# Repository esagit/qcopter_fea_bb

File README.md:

# Quadcopter - Breakout Board Adapter
Quadcopter - Breakout Board for Adafruit Feather 32u4 RFM9x LoRa Radio Module
* [Adafruit Feather 32u4 RFM9x LoRa Radio](https://www.adafruit.com/product/3078)

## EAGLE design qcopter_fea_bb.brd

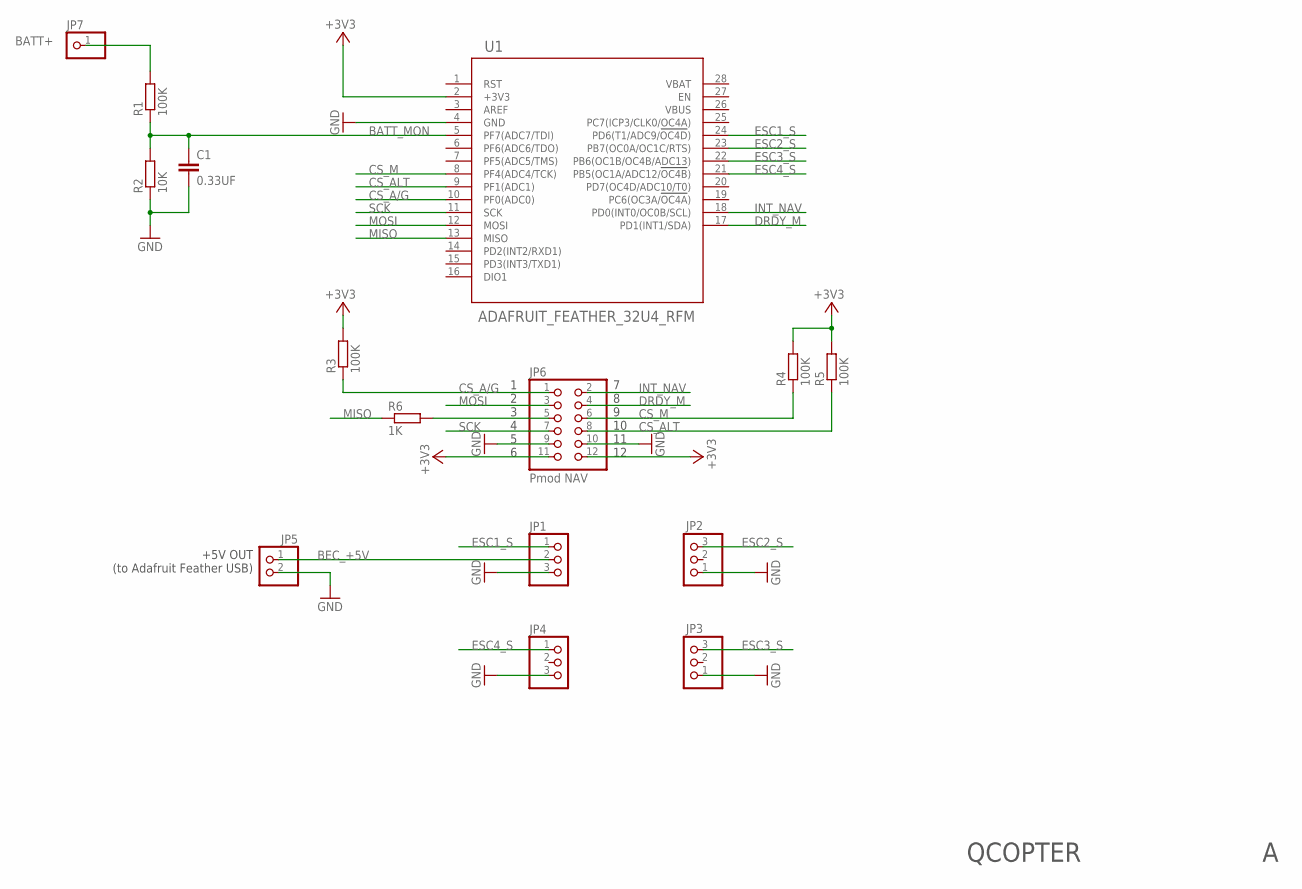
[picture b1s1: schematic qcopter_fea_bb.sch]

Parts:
C1: 0.33UF; C025-025X050
JP1, JP2, JP3, JP4: PINHD-1X3/90; 1X03/90
JP5: PINHD-1X2/90; 1X02/90
JP6: Pmod NAV; 2X06/90
JP7: PINHD-1X1; 1X01
R1, R3, R4, R5: 100K; 0207/10
R2: 10K; 0207/10
R6: 1K; 0207/10
U1: ADAFRUIT_FEATHER_32U4_RFM

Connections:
+3V3: JP6.11, JP6.12, R3.2, R4.2, R5.2, U1.2 (+3V3)
BATT+: JP7.1, R1.2
BATT_MON: C1.1, R1.1, R2.2, U1.5 (PF7(ADC7/TDI))
BEC_+5V: JP1.2, JP5.1
CS_A/G: JP6.1, R3.1, U1.10 (PF0(ADC0))
CS_ALT: JP6.8, R5.1, U1.9 (PF1(ADC1))
CS_M: JP6.6, R4.1, U1.8 (PF4(ADC4/TCK))
DRDY_M: JP6.4, U1.17 (PD1(INT1/SDA))
ESC1_S: JP1.1, U1.24 (PD6(T1/ADC9/OC4D))
ESC2_S: JP2.3, U1.23 (PB7(OC0A/OC1C/RTS))
ESC3_S: JP3.3, U1.22 (PB6(OC1B/OC4B/ADC13))
ESC4_S: JP4.1, U1.21 (PB5(OC1A/ADC12/OC4B))
GND: C1.2, JP1.3, JP2.1, JP3.1, JP4.3, JP5.2, JP6.9, JP6.10, R2.1, U1.4 (GND)
INT_NAV: JP6.2, U1.18 (PD0(INT0/OC0B/SCL))
MISO: R6.1, U1.13 (MISO)
MOSI: JP6.3, U1.12 (MOSI)
unnamed: JP6.5, R6.2
SCK: JP6.7, U1.11 (SCK)

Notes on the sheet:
1 2 3 4 5 6
7 8 9 10 11 12
+5V OUT (to Adafruit Feather USB)
QCOPTER

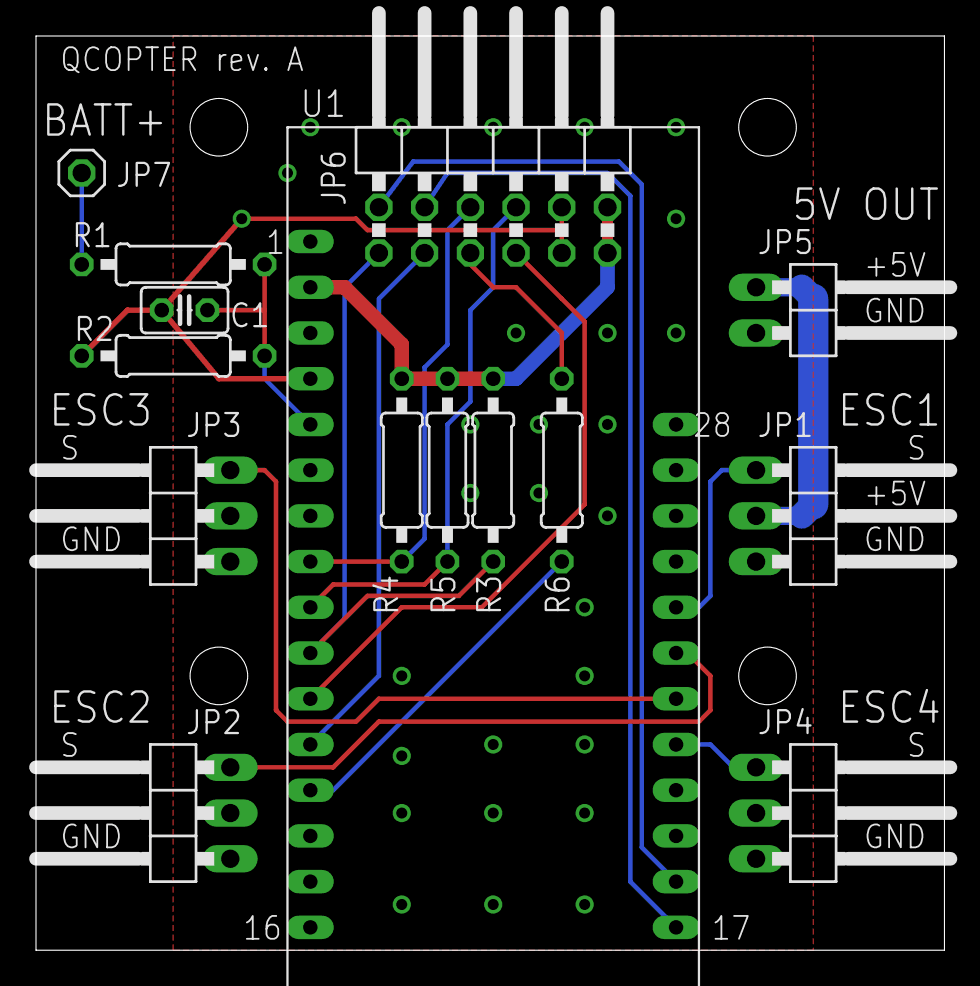
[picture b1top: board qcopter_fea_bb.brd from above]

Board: 2 copper layers, 50.5 x 50.8 mm, 15 parts (0 on the bottom side), 18 nets.

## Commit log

2017-08-24 :space_invader: Added .gitattributes & .gitignore files
2017-08-24 Initial commit
    Initial commit
2017-08-29 Added holes 4 x 3,2mm
    Added holes 4 x 3,2mm
2017-09-12 QCOPTER rev. A
    QCOPTER rev. A
2017-09-23 R1, R2 = 100K, C1 = 0,33F
    R1, R2 = 100K, C1 = 0,33F
2017-10-24 Lisätty .pdf Mottorit-ESCit-Pyörimissuunnat
    Lisätty .pdf Mottorit-ESCit-Pyörimissuunnat
